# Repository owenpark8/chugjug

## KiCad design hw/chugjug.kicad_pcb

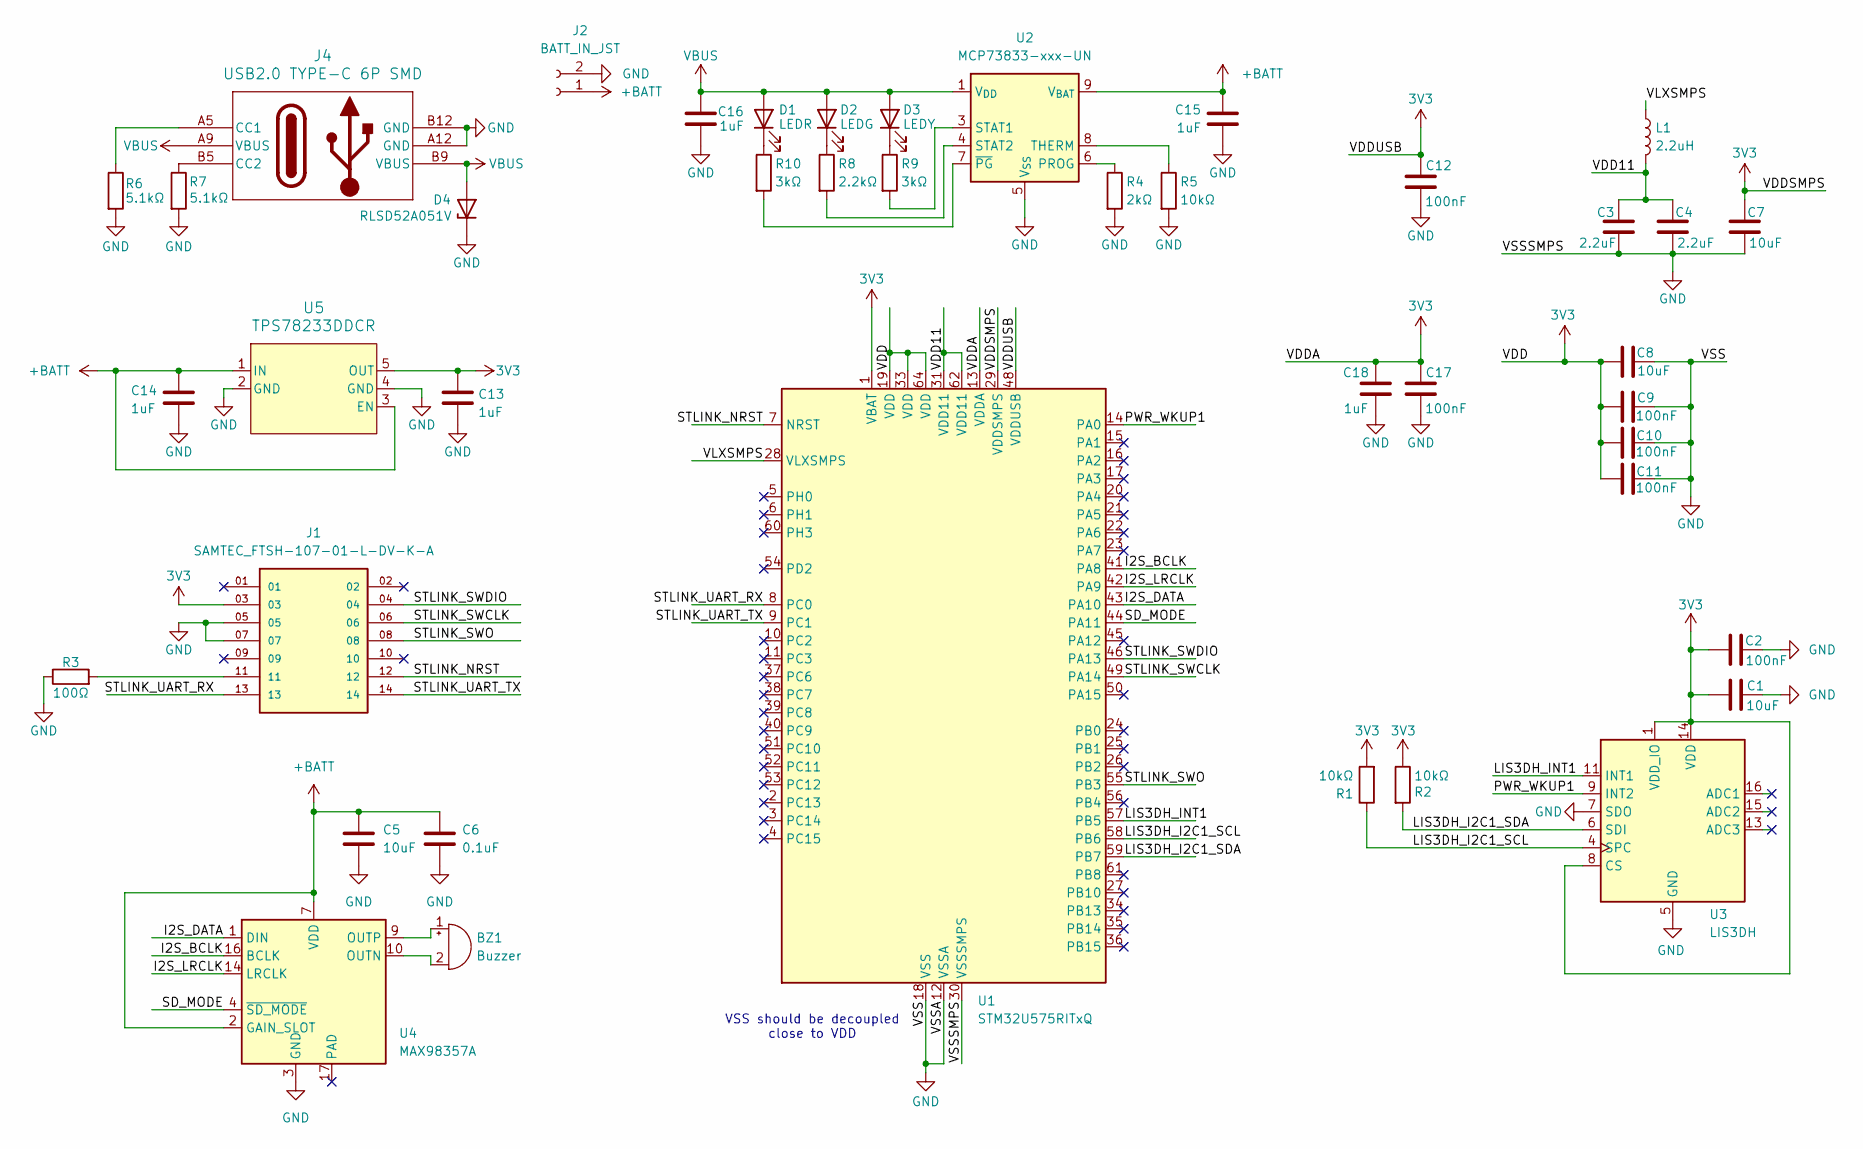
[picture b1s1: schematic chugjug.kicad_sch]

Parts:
BZ1: Buzzer; Buzzer_D20mm_H10mm_P10mm
C1, C5, C7, C8: 10uF; C_0805_2012Metric
C2, C9, C10, C11, C12, C17: 100nF; C_0402_1005Metric
C3, C4: 2.2uF; C_0603_1608Metric
C6: 0.1uF; C_0402_1005Metric
C13, C14, C15, C16, C18: 1uF; C_0402_1005Metric
D1: LEDR; LED_0603_1608Metric
D2: LEDG; LED_0805_2012Metric
D3: LEDY; LED_0805_2012Metric
D4: RLSD52A051V; D_SOD-523
J1: SAMTEC_FTSH-107-01-L-DV-K-A; PARTREV H
J2: BATT_IN_JST; JST_PH_S2B-PH-K_1x02_P2.00mm_Horizontal
J4: USB2.0 TYPE-C 6P SMD; MOLEX_CONN-RCP-USB2.0-C-6POS-SMD-RA-2171750001
L1: 2.2uH; L_0805_2012Metric
R1, R2, R5: 10kΩ; R_0402_1005Metric
R3: 100Ω; R_0402_1005Metric
R4: 2kΩ; R_0402_1005Metric
R6, R7: 5.1kΩ; R_0402_1005Metric
R8: 2.2kΩ; R_0402_1005Metric
R9, R10: 3kΩ; R_0402_1005Metric
U1: STM32U575RITxQ; LQFP-64_10x10mm_P0.5mm
U2: MCP73833-xxx-UN; MSOP-10_3x3mm_P0.5mm
U3: LIS3DH; LGA-16_3x3mm_P0.5mm_LayoutBorder3x5y
U4: MAX98357A; TQFN-16-1EP_3x3mm_P0.5mm_EP1.23x1.23mm
U5: TPS78233DDCR

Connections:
3V3: C1.1, C2.1, C7.1, C8.1, C9.2, C10.2, C11.2, C12.2, C13.1, C17.2, C18.2, J1.03, R1.2, R2.1, U1.1 (VBAT), U1.13 (VDDA), U1.19 (VDD), U1.29 (VDDSMPS), U1.33 (VDD), U1.48 (VDDUSB), U1.64 (VDD), U3.1 (VDD_IO), U3.8 (CS), U3.14 (VDD), U5.5 (OUT)
+BATT: C5.1, C6.1, C14.1, C15.1, J2.1, U2.9 (V_{BAT}), U2.10 (V_{BAT}), U4.2 (GAIN_SLOT), U4.7 (VDD), U4.8 (VDD), U5.1 (IN), U5.3 (EN)
/I2S_BCLK: U1.41 (PA8), U4.16 (BCLK)
/I2S_DATA: U1.43 (PA10), U4.1 (DIN)
/I2S_LRCLK: U1.42 (PA9), U4.14 (LRCLK)
/LIS3DH_I2C1_SCL: R1.1, U1.58 (PB6), U3.4 (SPC)
/LIS3DH_I2C1_SDA: R2.2, U1.59 (PB7), U3.6 (SDI)
/LIS3DH_INT1: U1.57 (PB5), U3.11 (INT1)
/PWR_WKUP1: U1.14 (PA0), U3.9 (INT2)
/SD_MODE: U1.44 (PA11), U4.4 (~SD_MODE)
/STLINK_NRST: J1.12, U1.7 (NRST)
/STLINK_SWCLK: J1.06, U1.49 (PA14)
/STLINK_SWDIO: J1.04, U1.46 (PA13)
/STLINK_SWO: J1.08, U1.55 (PB3)
/STLINK_UART_RX: J1.13, U1.8 (PC0)
/STLINK_UART_TX: J1.14, U1.9 (PC1)
/VDD11: C3.1, C4.1, L1.2, U1.31 (VDD11), U1.62 (VDD11)
/VLXSMPS: L1.1, U1.28 (VLXSMPS)
GND: C1.2, C2.2, C3.2, C4.2, C5.2, C6.2, C7.2, C8.2, C9.1, C10.1, C11.1, C12.1, C13.2, C14.2, C15.2, C16.2, C17.1, C18.1, D4.1 (K), J1.05, J1.07, J2.2, J4.A12 (GND), J4.B12 (GND), R3.1, R4.2, R5.2, R6.2, R7.2, U1.12 (VSSA), U1.18 (VSS), U1.30 (VSSSMPS), U1.32 (VSS), U1.47 (VSS), U1.63 (VSS), U2.5 (V_{SS}), U3.5 (GND), U3.7 (SDO), U3.10 (GND), U3.12 (GND), U4.3 (GND), U4.11 (GND), U4.15 (GND), U5.2 (GND), U5.4 (GND)
unnamed: BZ1.1 (+), U4.9 (OUTP)
unnamed: BZ1.2 (-), U4.10 (OUTN)
unnamed: D1.1 (K), R10.1
unnamed: D2.1 (K), R8.1
unnamed: D3.1 (K), R9.1
unnamed: J1.11, R3.2
unnamed: J4.A5 (CC1), R6.1
unnamed: J4.B5 (CC2), R7.1
unnamed: R4.1, U2.6 (PROG)
unnamed: R9.2, U2.3 (STAT1)
unnamed: R8.2, U2.4 (STAT2)
unnamed: R5.1, U2.8 (THERM)
unnamed: R10.2, U2.7 (~PG)
VBUS: C16.1, D1.2 (A), D2.2 (A), D3.2 (A), D4.2 (A), J4.A9 (VBUS), J4.B9 (VBUS), U2.1 (V_{DD}), U2.2 (V_{DD})

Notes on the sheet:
VSS should be decoupled close to VDD

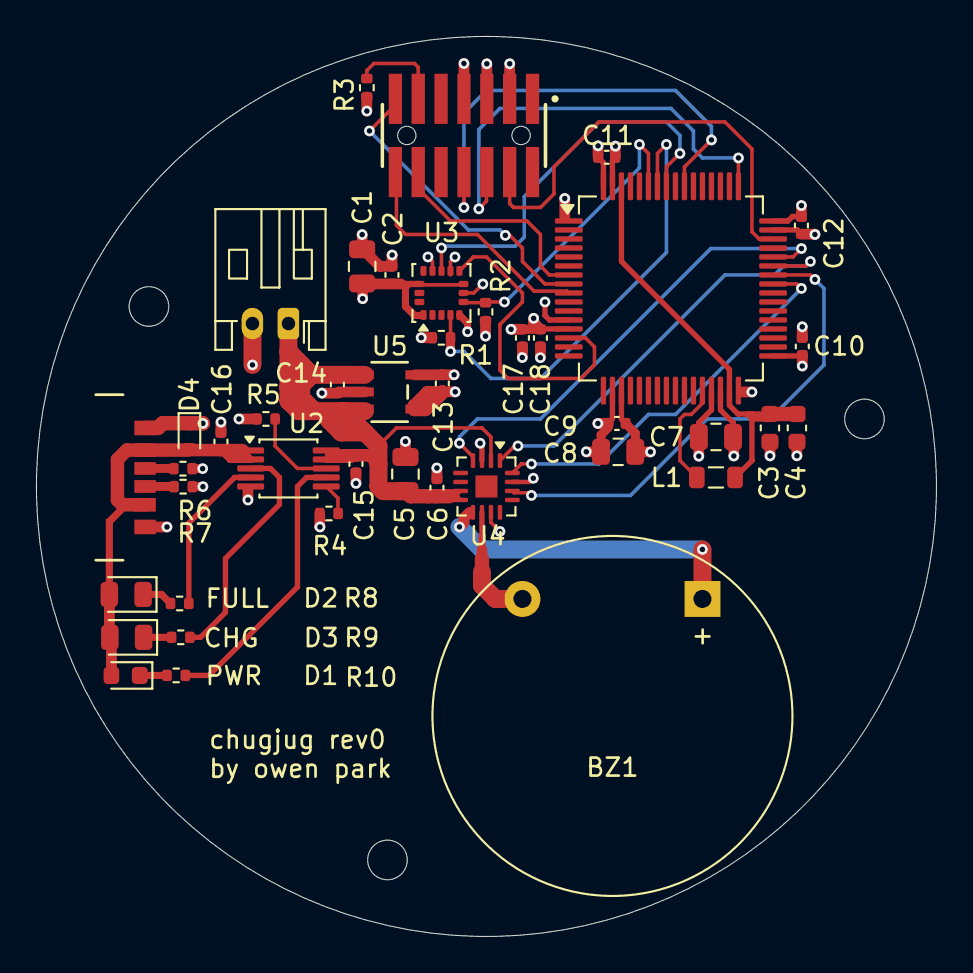
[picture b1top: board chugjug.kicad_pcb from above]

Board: 4 copper layers, 50.0 x 50.0 mm, 42 parts (0 on the bottom side), 33 nets.

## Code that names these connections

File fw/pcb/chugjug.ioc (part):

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Mcu.Name=STM32U575RITxQ
Mcu.Package=LQFP64
Mcu.UserName=STM32U575RITxQ
PA0.Mode=WakeUp1
PA0.Signal=PWR_WKUP1
PA10.GPIOParameters=GPIO_Label
PA10.GPIO_Label=I2S_DATA
PA10.Mode=SAI_A_Master
PA10.Signal=SAI1_SD_A
PA11.GPIOParameters=PinState,GPIO_Label
PA11.GPIO_Label=SD_MODE
PA11.PinState=GPIO_PIN_SET
PA11.Signal=GPIO_Output
PA13\ (JTMS/SWDIO).GPIOParameters=GPIO_Label
PA13\ (JTMS/SWDIO).GPIO_Label=STLINK_SWDIO
PA13\ (JTMS/SWDIO).Mode=Trace_Asynchronous_SW
PA13\ (JTMS/SWDIO).Signal=DEBUG_JTMS-SWDIO
PA14\ (JTCK/SWCLK).GPIOParameters=GPIO_Label
PA14\ (JTCK/SWCLK).GPIO_Label=STLINK_SWCLK
PA14\ (JTCK/SWCLK).Mode=Trace_Asynchronous_SW
PA14\ (JTCK/SWCLK).Signal=DEBUG_JTCK-SWCLK
PA5.Mode=CSLEEP
PA5.Signal=PWR_CSLEEP
PA6.Mode=CDSTOP
PA6.Signal=PWR_CDSTOP
PA8.GPIOParameters=GPIO_Label
PA8.GPIO_Label=I2S_BCLK
PA8.Mode=SAI_A_Master
PA8.Signal=SAI1_SCK_A
PA9.GPIOParameters=GPIO_Label
PA9.GPIO_Label=I2S_LRCLK
PA9.Mode=SAI_A_Master
PA9.Signal=SAI1_FS_A
PB3\ (JTDO/TRACESWO).GPIOParameters=GPIO_Label
PB3\ (JTDO/TRACESWO).GPIO_Label=STLINK_SWO
PB3\ (JTDO/TRACESWO).Mode=Trace_Asynchronous_SW
PB3\ (JTDO/TRACESWO).Signal=DEBUG_JTDO-SWO
PB5.GPIOParameters=GPIO_Label
PB5.GPIO_Label=LIS3DH_INT1
PB5.Signal=GPIO_Input
PB6.GPIOParameters=GPIO_Label
PB6.GPIO_Label=LIS3DH_I2C1_SCL
PB6.Mode=I2C
PB6.Signal=I2C1_SCL
PB7.GPIOParameters=GPIO_Label
PB7.GPIO_Label=LIS3DH_I2C1_SDA
PB7.Mode=I2C
PB7.Signal=I2C1_SDA
PC0.GPIOParameters=GPIO_Label
PC0.GPIO_Label=STLINK_UART_RX
PC0.Mode=Asynchronous
PC0.Signal=LPUART1_RX
PC1.GPIOParameters=GPIO_Label
PC1.GPIO_Label=STLINK_UART_TX
PC1.Mode=Asynchronous
PC1.Signal=LPUART1_TX
RCC.HSE_VALUE=16000000
RCC.SYSCLKFreq_VALUE=48000000
board=custom

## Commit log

2026-04-04 init: initial firmware and schematic
2026-04-04 combine git ignores
2026-04-04 add nucleo project
2026-04-04 enable c++17
2026-04-04 clang format and tidy
2026-04-05 reading from lis3dh working
2026-04-06 move reading of accelerometer to timer and get high z interrupt working
2026-04-07 standby mode and wakeup working
2026-04-09 loading chugjug sound from flash
2026-04-12 sound effects working
2026-04-12 hw: add 3v3 lod and stlink header
2026-05-10 add pcb headers and ldo
2026-05-10 finish schematic (i think)
2026-05-11 lots of layout progress
2026-05-13 much more layout changes. amp powered from +batt now
2026-05-18 initial layout done
2026-05-30 finalize pcb for jlcpcb ordering
